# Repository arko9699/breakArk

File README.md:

# breakArk
 A simple breakout board designed for use with handwired projects. Allows controller boards to be socketed and thus easily replaced

# Pictures

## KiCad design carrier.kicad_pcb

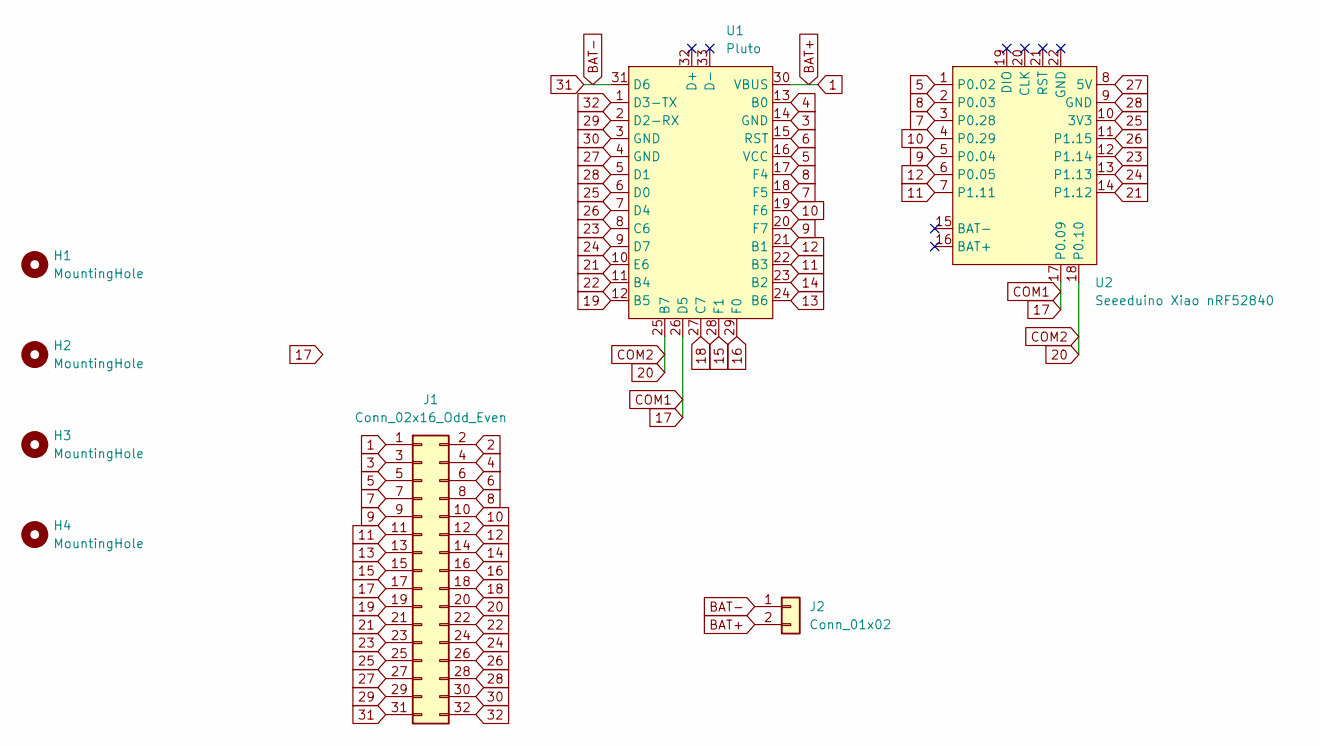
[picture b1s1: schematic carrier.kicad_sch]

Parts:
H1, H2, H3, H4: MountingHole; MountingHole_2.2mm_M2
J1: Conn_02x16_Odd_Even; PinHeader_2x16_P2.54mm_Horizontal
J2: Conn_01x02; PinHeader_1x02_P2.54mm_Vertical
U1: Pluto; Pluto_AH_USBup
U2: Seeeduino Xiao nRF52840; Xiao_nRF52840_ACH

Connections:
1: J1.1, J2.2, U1.30 (VBUS)
2: J1.2
3: J1.3, U1.14 (GND)
4: J1.4, U1.13 (B0)
5: J1.5, U1.16 (VCC), U2.1 (P0.02)
6: J1.6, U1.15 (RST)
7: J1.7, U1.18 (F5), U2.3 (P0.28)
8: J1.8, U1.17 (F4), U2.2 (P0.03)
9: J1.9, U1.20 (F7), U2.5 (P0.04)
10: J1.10, U1.19 (F6), U2.4 (P0.29)
11: J1.11, U1.22 (B3), U2.7 (P1.11)
12: J1.12, U1.21 (B1), U2.6 (P0.05)
13: J1.13, U1.24 (B6)
14: J1.14, U1.23 (B2)
15: J1.15, U1.28 (F1)
16: J1.16, U1.29 (F0)
17: J1.17, U1.26 (D5), U2.17 (P0.09)
18: J1.18, U1.27 (C7)
19: J1.19, U1.12 (B5)
20: J1.20, U1.25 (B7), U2.18 (P0.10)
21: J1.21, U1.10 (E6), U2.14 (P1.12)
22: J1.22, U1.11 (B4)
23: J1.23, U1.8 (C6), U2.12 (P1.14)
24: J1.24, U1.9 (D7), U2.13 (P1.13)
25: J1.25, U1.6 (D0), U2.10 (3V3)
26: J1.26, U1.7 (D4), U2.11 (P1.15)
27: J1.27, U1.4 (GND), U2.8 (5V)
28: J1.28, U1.5 (D1), U2.9 (GND)
29: J1.29, U1.2 (D2-RX)
30: J1.30, U1.3 (GND)
31: J1.31, J2.1, U1.31 (D6)
32: J1.32, U1.1 (D3-TX)

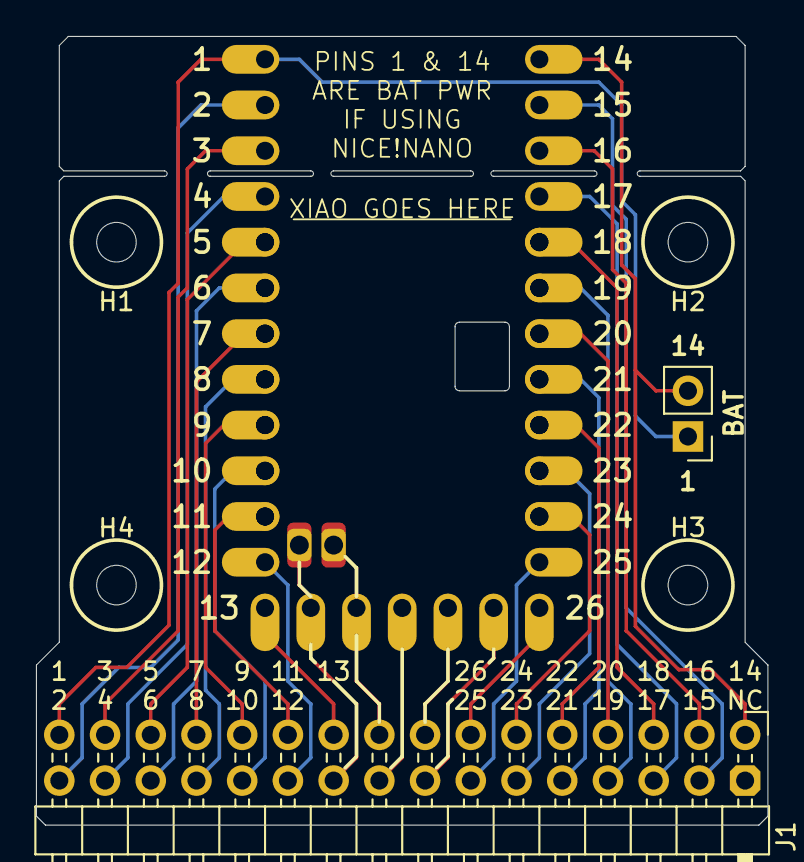
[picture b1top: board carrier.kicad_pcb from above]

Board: 2 copper layers, 40.6 x 43.8 mm, 8 parts (1 on the bottom side), 31 nets.

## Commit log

2024-05-21 Uploaded all files
2024-05-21 Pictures for reference
